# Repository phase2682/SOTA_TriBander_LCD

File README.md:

# SOTA_TriBander_LCD
Replacing the LED display with a LCD on the SOTA  Tri-Bander CW transceiver
https://www.ai6xg.com/post/lcd-display-for-the-kd1jv-tribander

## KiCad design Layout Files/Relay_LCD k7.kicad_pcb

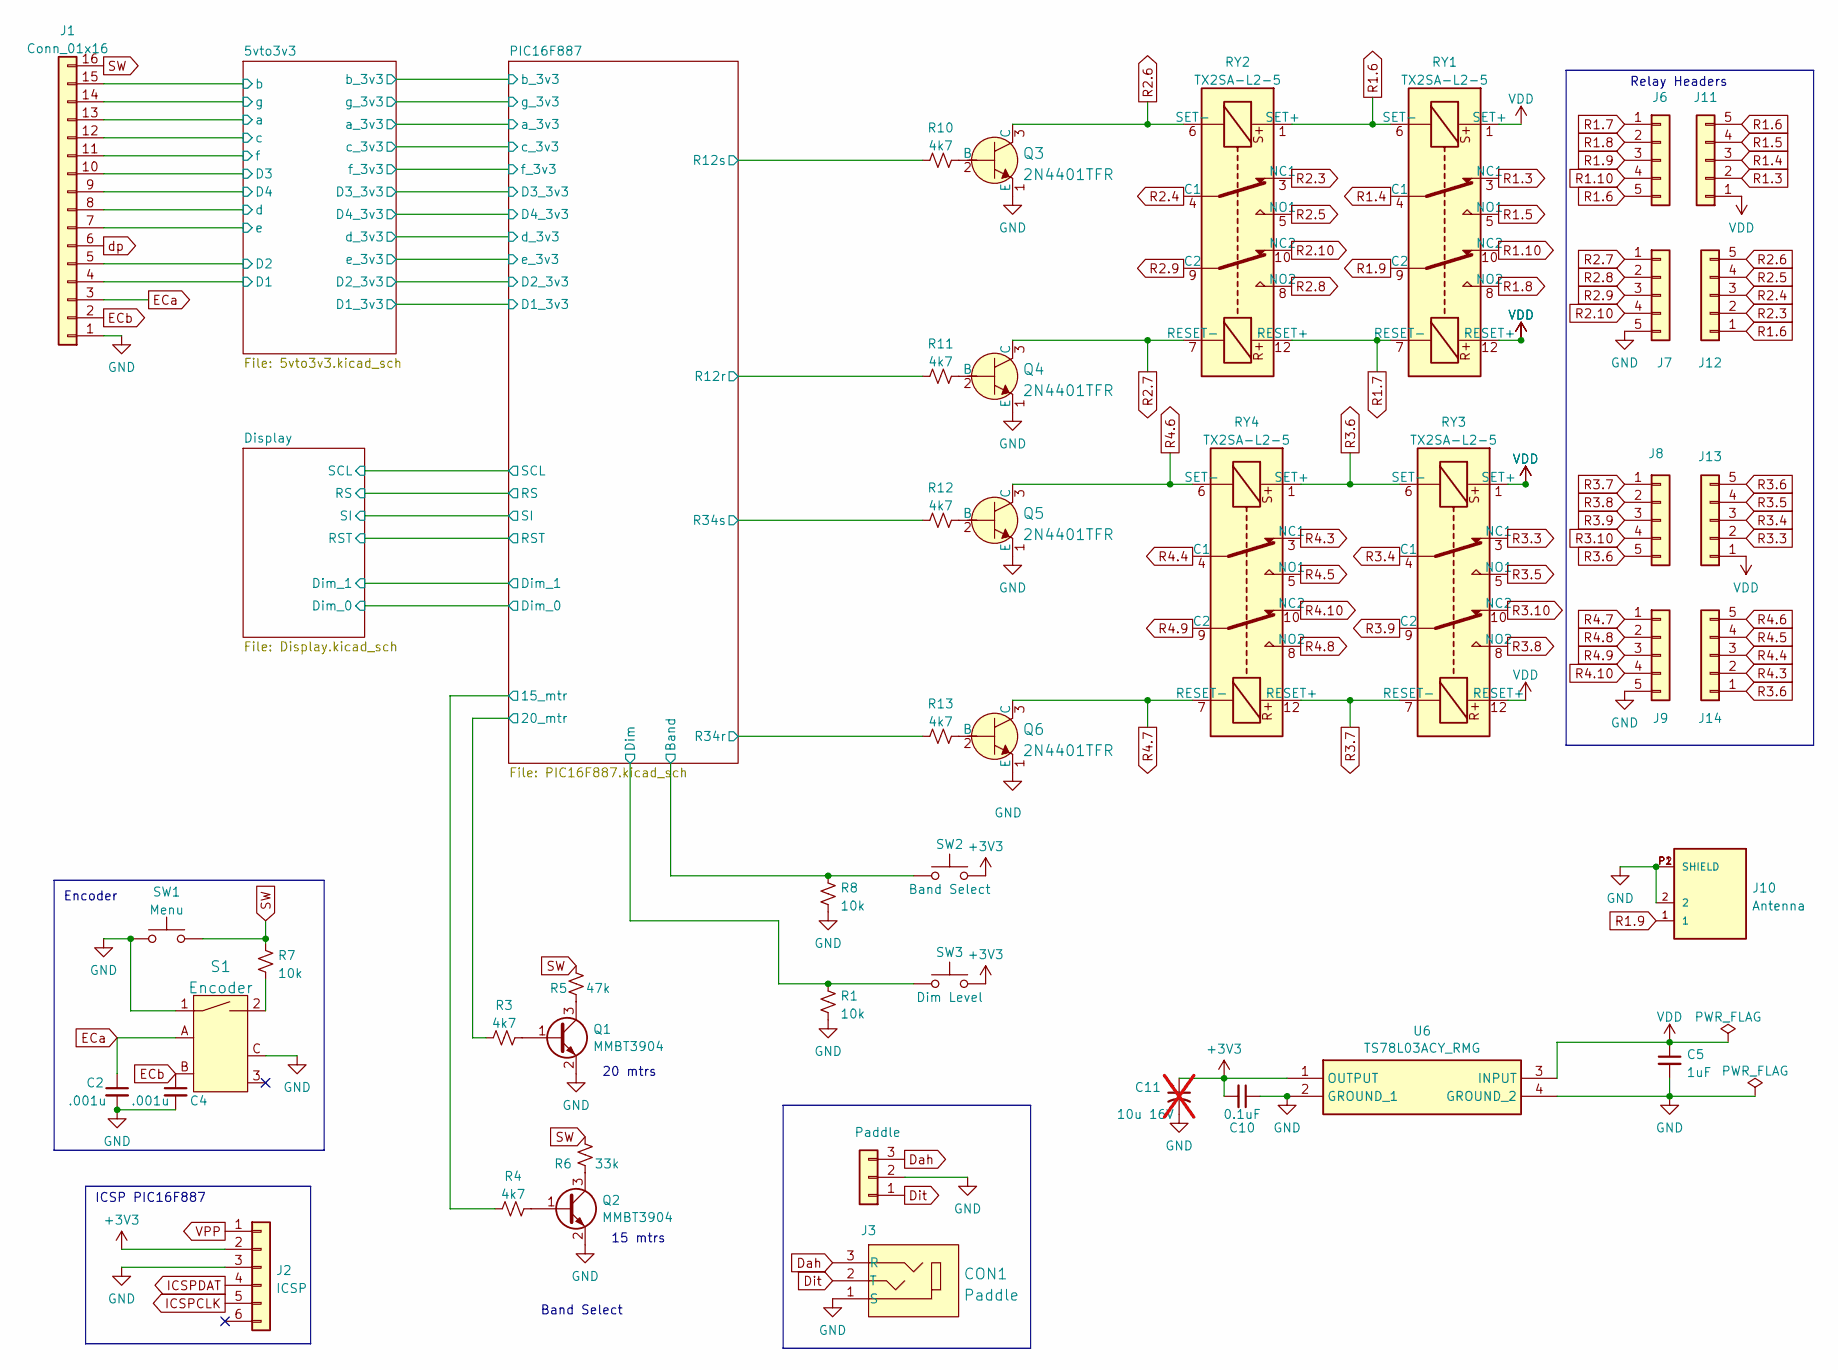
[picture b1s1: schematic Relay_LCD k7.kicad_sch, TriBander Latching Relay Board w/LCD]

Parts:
C2, C4: .001u; C_Disc_D3.4mm_W2.1mm_P2.50mm
C5: 1uF; C_1206_3216Metric_Pad1.33x1.80mm_HandSolder
C10: 0.1uF; C_1206_3216Metric_Pad1.33x1.80mm_HandSolder
C11: 10u 16V; CP_Radial_D6.3mm_P2.50mm; not fitted
CON1: Paddle; CUI_SJ1-3513N round pin; MPN SJ1-3523N; Digi-Key_PN CP1-3523N-ND
J1: Conn_01x16; PinHeader_1x16_P2.54mm_Vertical
J2: ICSP; PinHeader_1x06_P2.54mm_Vertical
J3: Paddle; PinHeader_1x03_P2.54mm_Vertical
J6, J7, J8, J9, J11, J12, J13, J14: Conn_01x05; PinHeader_1x05_P2.54mm_Vertical
J10: Antenna; CONN_1-1337543-0
Q1, Q2: MMBT3904; SOT-23
Q3, Q4, Q5, Q6: 2N4401TFR; TO-92-3_Formed_Leads; MPN 2N4401TFR; Digi-Key_PN 2N4401D26ZCT-ND
R1, R7, R8: 10k; R_1206_3216Metric_Pad1.30x1.75mm_HandSolder
R3, R4: 4k7; R_1206_3216Metric_Pad1.30x1.75mm_HandSolder
R5: 47k; R_1206_3216Metric_Pad1.30x1.75mm_HandSolder
R6: 33k; R_1206_3216Metric_Pad1.30x1.75mm_HandSolder
R10, R11, R12, R13: 4k7; R THT .25W minP
RY1, RY2, RY3, RY4: TX2SA-L2-5; Relay_DPDT_Kemet_EE2_NU_DoubleCoil
S1: Encoder; Rotary_Encoder_Switched_PEC11R; MPN PEC11R-4215F-S0024; Digi-Key_PN PEC11R-4215F-S0024-ND
SW1: Menu; SW_PUSH_6mm
SW2: Band Select; SW_PUSH_6mm
SW3: Dim Level; SW_PUSH_6mm
U6: TS78L03ACY_RMG; SOT-89-3_Handsoldering; Mouser Part Number 821-TS78L03ACYRMG

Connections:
+3V3: C10.2, C11.1, J2.2, SW2.2, SW3.2, U6.1 (OUTPUT); also elsewhere on the board
/5vto3v3/D1: J1.4; also elsewhere on the board
/5vto3v3/D2: J1.5; also elsewhere on the board
/5vto3v3/D3: J1.10; also elsewhere on the board
/5vto3v3/D4: J1.9; also elsewhere on the board
/5vto3v3/a: J1.13; also elsewhere on the board
/5vto3v3/b: J1.15; also elsewhere on the board
/5vto3v3/c: J1.12; also elsewhere on the board
/5vto3v3/d: J1.8; also elsewhere on the board
/5vto3v3/e: J1.7; also elsewhere on the board
/5vto3v3/f: J1.11; also elsewhere on the board
/5vto3v3/g: J1.14; also elsewhere on the board
/PIC16F887/15_mtr: R4.1; also elsewhere on the board
/PIC16F887/20_mtr: R3.1; also elsewhere on the board
/PIC16F887/Band: R8.2, SW2.1; also elsewhere on the board
/PIC16F887/Dim: R1.2, SW3.1; also elsewhere on the board
/PIC16F887/R12r: R11.1; also elsewhere on the board
/PIC16F887/R12s: R10.1; also elsewhere on the board
/PIC16F887/R34r: R13.1; also elsewhere on the board
/PIC16F887/R34s: R12.1; also elsewhere on the board
Dah: CON1.3 (R), J3.3
Dit: CON1.2 (T), J3.1
ECa: C2.1, J1.3, S1.A (CH_A)
ECb: C4.1, J1.2, S1.B (CH_B)
GND: C2.2, C4.2, C5.2, C10.1, C11.2, CON1.1 (S), J1.1, J2.3, J3.2, J7.5, J9.5, J10.2, J10.P1 (SHIELD), J10.P2 (SHIELD), Q1.2 (E), Q2.2 (E), Q3.1 (E), Q4.1 (E), Q5.1 (E), Q6.1 (E), R1.1, R8.1, S1.1, S1.C (COM), SW1.1, U6.2 (GROUND_1), U6.4 (GROUND_2); also elsewhere on the board
ICSPCLK: J2.5; also elsewhere on the board
ICSPDAT: J2.4; also elsewhere on the board
unnamed: Q1.1 (B), R3.2
unnamed: Q1.3 (C), R5.2
unnamed: Q2.1 (B), R4.2
unnamed: Q2.3 (C), R6.2
unnamed: Q3.2 (B), R10.2
unnamed: Q4.2 (B), R11.2
unnamed: Q5.2 (B), R12.2
unnamed: Q6.2 (B), R13.2
unnamed: R7.2, S1.2
R1.3: J11.2, RY1.3 (NC1)
R1.4: J11.3, RY1.4 (C1)
R1.5: J11.4, RY1.5 (NO1)
R1.6: J6.5, J11.5, J12.1, RY1.6 (SET-), RY2.1 (SET+)
R1.7: J6.1, RY1.7 (RESET-), RY2.12 (RESET+)
R1.8: J6.2, RY1.8 (NO2)
R1.9: J6.3, J10.1, RY1.9 (C2)
R1.10: J6.4, RY1.10 (NC2)
R2.3: J12.2, RY2.3 (NC1)
R2.4: J12.3, RY2.4 (C1)
R2.5: J12.4, RY2.5 (NO1)
R2.6: J12.5, Q3.3 (C), RY2.6 (SET-)
R2.7: J7.1, Q4.3 (C), RY2.7 (RESET-)
R2.8: J7.2, RY2.8 (NO2)
R2.9: J7.3, RY2.9 (C2)
R2.10: J7.4, RY2.10 (NC2)
R3.3: J13.2, RY3.3 (NC1)
R3.4: J13.3, RY3.4 (C1)
R3.5: J13.4, RY3.5 (NO1)
R3.6: J8.5, J13.5, J14.1, RY3.6 (SET-), RY4.1 (SET+)
R3.7: J8.1, RY3.7 (RESET-), RY4.12 (RESET+)
R3.8: J8.2, RY3.8 (NO2)
R3.9: J8.3, RY3.9 (C2)
R3.10: J8.4, RY3.10 (NC2)
R4.3: J14.2, RY4.3 (NC1)
R4.4: J14.3, RY4.4 (C1)
R4.5: J14.4, RY4.5 (NO1)
R4.6: J14.5, Q5.3 (C), RY4.6 (SET-)
R4.7: J9.1, Q6.3 (C), RY4.7 (RESET-)
R4.8: J9.2, RY4.8 (NO2)
R4.9: J9.3, RY4.9 (C2)
R4.10: J9.4, RY4.10 (NC2)
SW: J1.16, R5.1, R6.1, R7.1, SW1.2
VDD: C5.1, J11.1, J13.1, RY1.1 (SET+), RY1.12 (RESET+), RY3.1 (SET+), RY3.12 (RESET+), U6.3 (INPUT)
VPP: J2.1; also elsewhere on the board
dp: J1.6

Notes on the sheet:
20 mtrs
15 mtrs
Relay Headers
ICSP PIC16F887
Encoder
Band Select

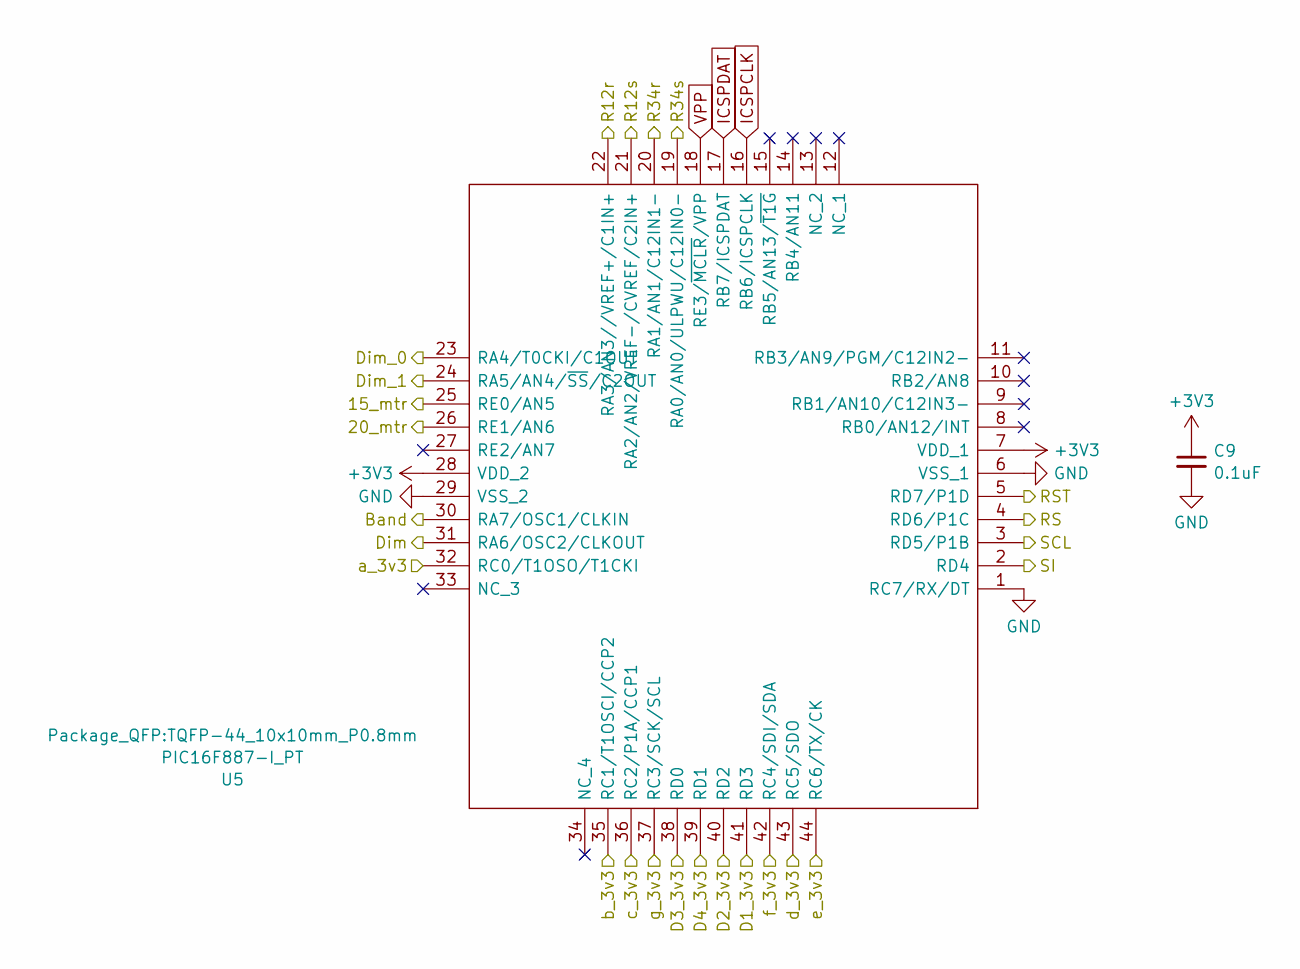
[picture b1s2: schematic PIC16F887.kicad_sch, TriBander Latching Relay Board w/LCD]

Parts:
C9: 0.1uF; C_1206_3216Metric_Pad1.33x1.80mm_HandSolder
U5: PIC16F887-I_PT; TQFP-44_10x10mm_P0.8mm; Mouser Part Number 579-PIC16F887-I/PT

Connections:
+3V3: C9.1, U5.7 (VDD_1), U5.28 (VDD_2); also elsewhere on the board
/5vto3v3/D1_3v3: U5.41 (RD3); also elsewhere on the board
/5vto3v3/D2_3v3: U5.40 (RD2); also elsewhere on the board
/5vto3v3/D3_3v3: U5.38 (RD0); also elsewhere on the board
/5vto3v3/D4_3v3: U5.39 (RD1); also elsewhere on the board
/5vto3v3/a_3v3: U5.32 (RC0/T1OSO/T1CKI); also elsewhere on the board
/5vto3v3/b_3v3: U5.35 (RC1/T1OSCI/CCP2); also elsewhere on the board
/5vto3v3/c_3v3: U5.36 (RC2/P1A/CCP1); also elsewhere on the board
/5vto3v3/d_3v3: U5.43 (RC5/SDO); also elsewhere on the board
/5vto3v3/e_3v3: U5.44 (RC6/TX/CK); also elsewhere on the board
/5vto3v3/f_3v3: U5.42 (RC4/SDI/SDA); also elsewhere on the board
/5vto3v3/g_3v3: U5.37 (RC3/SCK/SCL); also elsewhere on the board
/Display/Dim_0: U5.23 (RA4/T0CKI/C1OUT); also elsewhere on the board
/Display/Dim_1: U5.24 (RA5/AN4/~SS/C2OUT); also elsewhere on the board
/Display/RS: U5.4 (RD6/P1C); also elsewhere on the board
/Display/RST: U5.5 (RD7/P1D); also elsewhere on the board
/Display/SCL: U5.3 (RD5/P1B); also elsewhere on the board
/Display/SI: U5.2 (RD4); also elsewhere on the board
/PIC16F887/15_mtr: U5.25 (RE0/AN5); also elsewhere on the board
/PIC16F887/20_mtr: U5.26 (RE1/AN6); also elsewhere on the board
/PIC16F887/Band: U5.30 (RA7/OSC1/CLKIN); also elsewhere on the board
/PIC16F887/Dim: U5.31 (RA6/OSC2/CLKOUT); also elsewhere on the board
/PIC16F887/R12r: U5.22 (RA3/AN3//VREF+/C1IN+); also elsewhere on the board
/PIC16F887/R12s: U5.21 (RA2/AN2/VREF-/CVREF/C2IN+); also elsewhere on the board
/PIC16F887/R34r: U5.20 (RA1/AN1/C12IN1-); also elsewhere on the board
/PIC16F887/R34s: U5.19 (RA0/AN0/ULPWU/C12IN0-); also elsewhere on the board
GND: C9.2, U5.1 (RC7/RX/DT), U5.6 (VSS_1), U5.29 (VSS_2); also elsewhere on the board
ICSPCLK: U5.16 (RB6/ICSPCLK); also elsewhere on the board
ICSPDAT: U5.17 (RB7/ICSPDAT); also elsewhere on the board
VPP: U5.18 (RE3/~MCLR/VPP); also elsewhere on the board

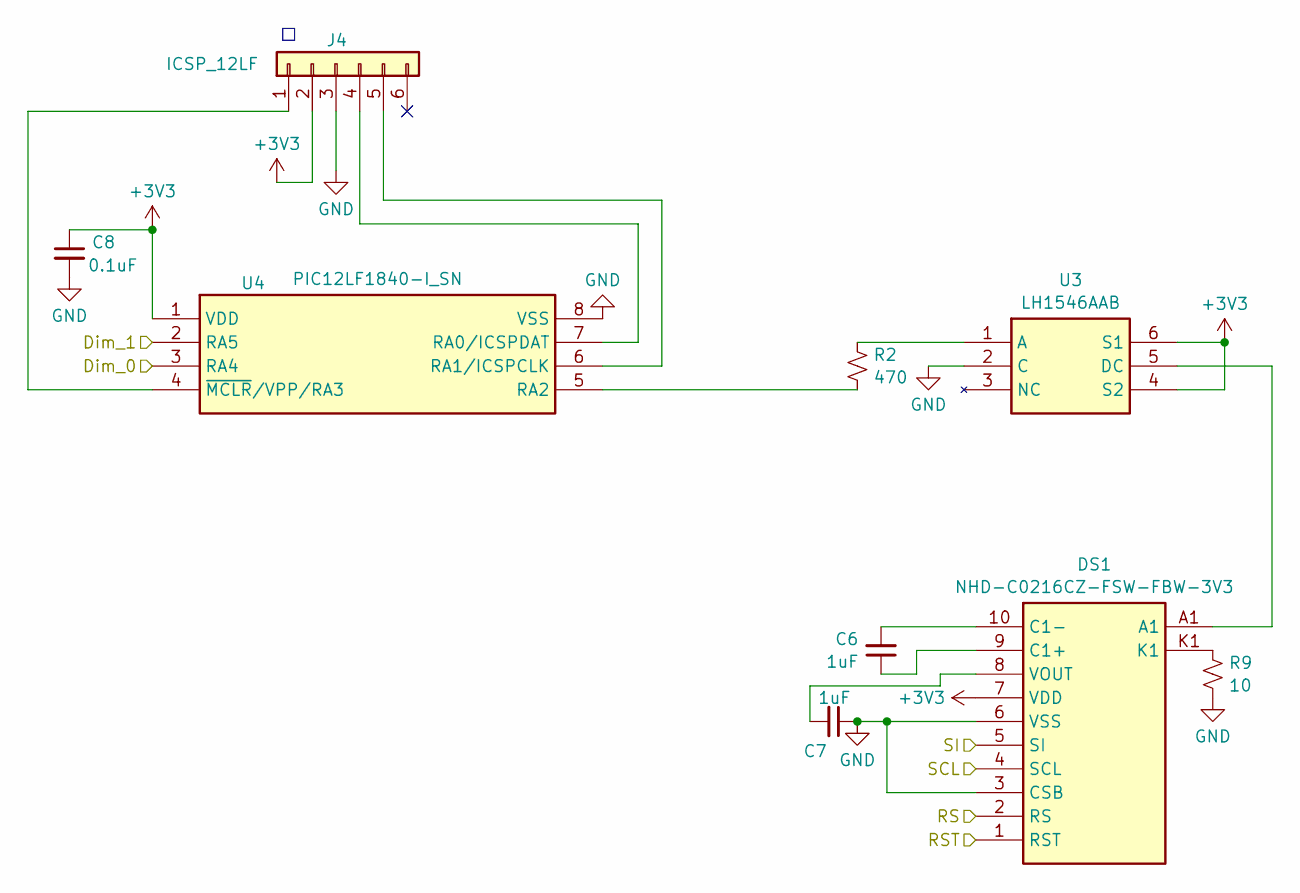
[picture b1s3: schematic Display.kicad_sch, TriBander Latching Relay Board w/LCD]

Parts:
C6, C7: 1uF; C_1206_3216Metric_Pad1.33x1.80mm_HandSolder
C8: 0.1uF; C_1206_3216Metric_Pad1.33x1.80mm_HandSolder
DS1: NHD-C0216CZ-FSW-FBW-3V3; NHDC0216CZFSWFBW3V3; Mouser Part Number 763-C0216CZ-FSWFBW3V
J4: ICSP_12LF; PinHeader_1x06_P2.54mm_Vertical
R2: 470; R_1206_3216Metric_Pad1.30x1.75mm_HandSolder
R9: 10; R_1206_3216Metric_Pad1.30x1.75mm_HandSolder
U3: LH1546AAB; SOP254P980X425-6N; Mouser Part Number 782-LH1546AABTR
U4: PIC12LF1840-I_SN; SO-8_3.9x4.9mm_P1.27mm; Mouser Part Number 579-PIC12LF1840-I/SN

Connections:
+3V3: C8.1, DS1.7 (VDD), J4.2, U3.4 (S2), U3.6 (S1), U4.1 (VDD); also elsewhere on the board
/Display/Dim_0: U4.3 (RA4); also elsewhere on the board
/Display/Dim_1: U4.2 (RA5); also elsewhere on the board
/Display/RS: DS1.2 (RS); also elsewhere on the board
/Display/RST: DS1.1 (RST); also elsewhere on the board
/Display/SCL: DS1.4 (SCL); also elsewhere on the board
/Display/SI: DS1.5 (SI); also elsewhere on the board
GND: C7.1, C8.2, DS1.3 (CSB), DS1.6 (VSS), J4.3, R9.2, U3.2 (C), U4.8 (VSS); also elsewhere on the board
unnamed: C6.1, DS1.9 (C1+)
unnamed: C6.2, DS1.10 (C1-)
unnamed: DS1.K1, R9.1
unnamed: C7.2, DS1.8 (VOUT)
unnamed: J4.1, U4.4 (~MCLR/VPP/RA3)
unnamed: J4.4, U4.7 (RA0/ICSPDAT)
unnamed: J4.5, U4.6 (RA1/ICSPCLK)
unnamed: R2.1, U3.1 (A)
unnamed: DS1.A1, U3.5 (DC)
unnamed: R2.2, U4.5 (RA2)

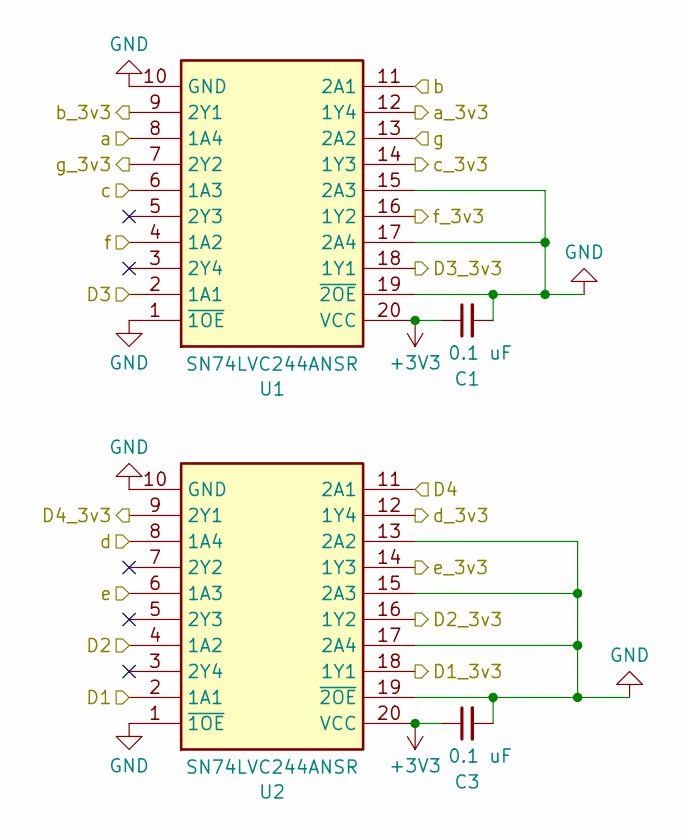
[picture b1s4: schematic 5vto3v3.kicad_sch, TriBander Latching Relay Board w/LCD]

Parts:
C1, C3: 0.1 uF; C_1206_3216Metric_Pad1.33x1.80mm_HandSolder
U1, U2: SN74LVC244ANSR; SO-20_5.3x12.6mm_P1.27mm; Mouser Part Number 595-SN74LVC244ANSR

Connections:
+3V3: C1.1, C3.1, U1.20 (VCC), U2.20 (VCC); also elsewhere on the board
/5vto3v3/D1: U2.2 (1A1); also elsewhere on the board
/5vto3v3/D1_3v3: U2.18 (1Y1); also elsewhere on the board
/5vto3v3/D2: U2.4 (1A2); also elsewhere on the board
/5vto3v3/D2_3v3: U2.16 (1Y2); also elsewhere on the board
/5vto3v3/D3: U1.2 (1A1); also elsewhere on the board
/5vto3v3/D3_3v3: U1.18 (1Y1); also elsewhere on the board
/5vto3v3/D4: U2.11 (2A1); also elsewhere on the board
/5vto3v3/D4_3v3: U2.9 (2Y1); also elsewhere on the board
/5vto3v3/a: U1.8 (1A4); also elsewhere on the board
/5vto3v3/a_3v3: U1.12 (1Y4); also elsewhere on the board
/5vto3v3/b: U1.11 (2A1); also elsewhere on the board
/5vto3v3/b_3v3: U1.9 (2Y1); also elsewhere on the board
/5vto3v3/c: U1.6 (1A3); also elsewhere on the board
/5vto3v3/c_3v3: U1.14 (1Y3); also elsewhere on the board
/5vto3v3/d: U2.8 (1A4); also elsewhere on the board
/5vto3v3/d_3v3: U2.12 (1Y4); also elsewhere on the board
/5vto3v3/e: U2.6 (1A3); also elsewhere on the board
/5vto3v3/e_3v3: U2.14 (1Y3); also elsewhere on the board
/5vto3v3/f: U1.4 (1A2); also elsewhere on the board
/5vto3v3/f_3v3: U1.16 (1Y2); also elsewhere on the board
/5vto3v3/g: U1.13 (2A2); also elsewhere on the board
/5vto3v3/g_3v3: U1.7 (2Y2); also elsewhere on the board
GND: C1.2, C3.2, U1.1 (~1OE), U1.10 (GND), U1.15 (2A3), U1.17 (2A4), U1.19 (~2OE), U2.1 (~1OE), U2.10 (GND), U2.13 (2A2), U2.15 (2A3), U2.17 (2A4), U2.19 (~2OE); also elsewhere on the board

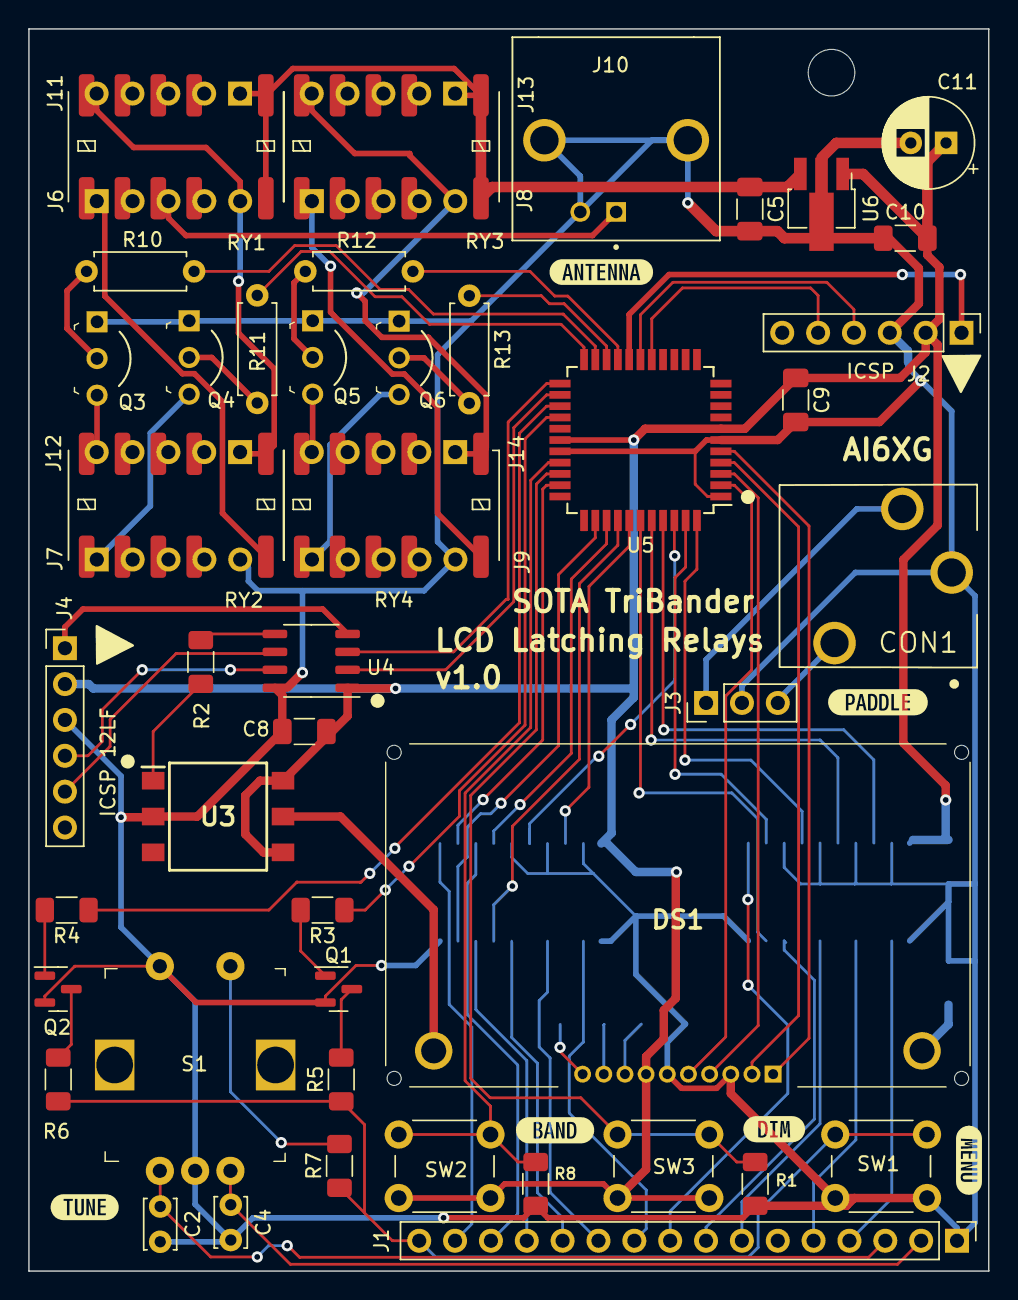
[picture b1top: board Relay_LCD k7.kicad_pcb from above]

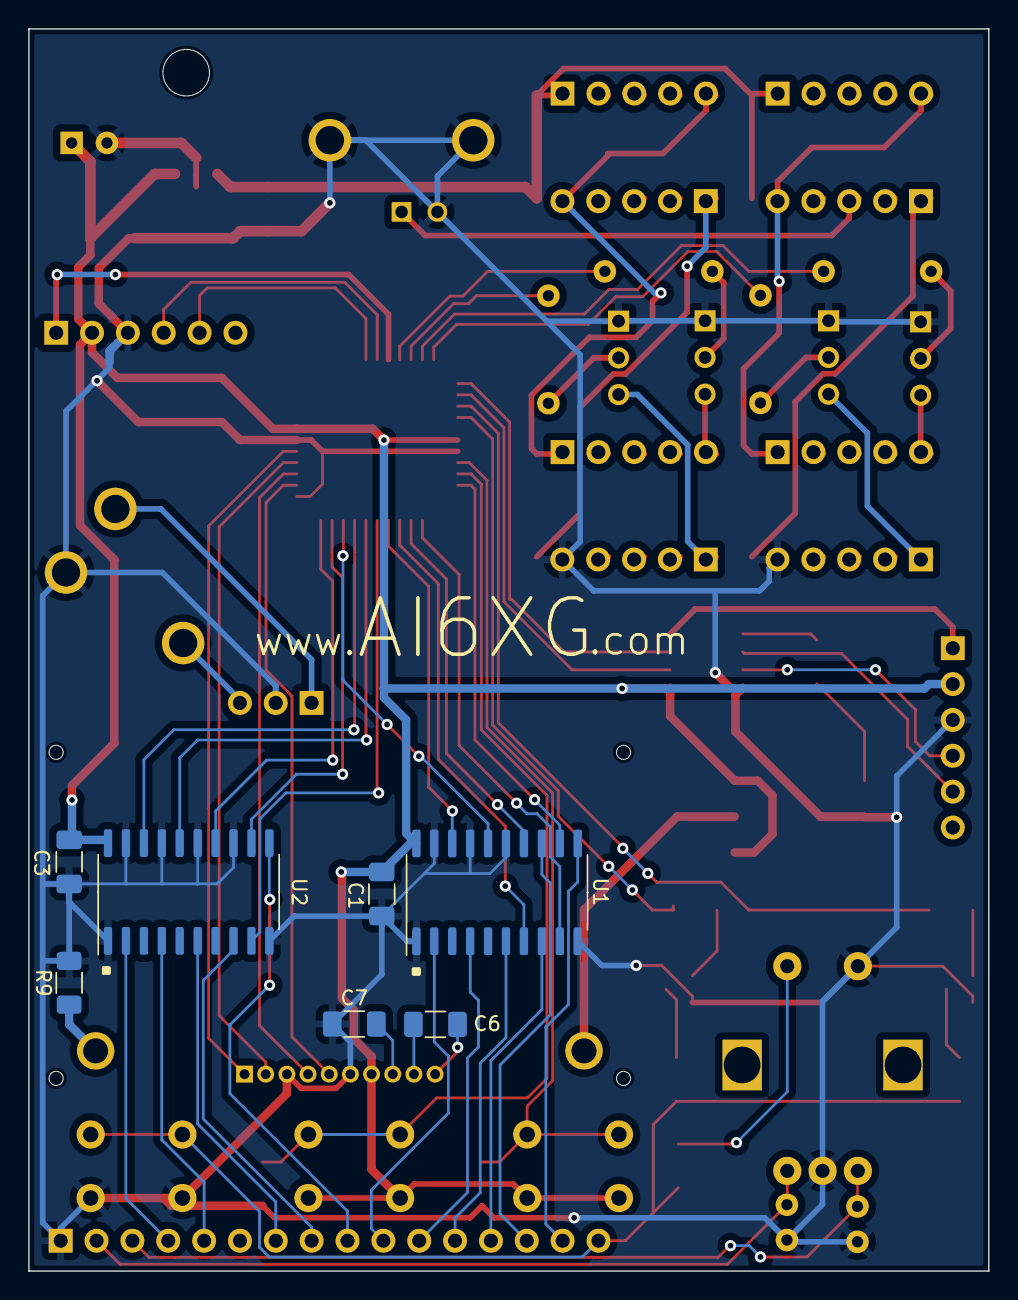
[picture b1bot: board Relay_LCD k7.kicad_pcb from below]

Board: 2 copper layers, 68.0 x 88.0 mm, 65 parts (7 on the bottom side), 98 nets.

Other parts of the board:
kibuzzard-659F9941: G***; kibuzzard-659F9941
kibuzzard-659F9955: G***; kibuzzard-659F9955
kibuzzard-6406D9A6: G***; kibuzzard-6406D9A6
kibuzzard-6406D9EC: G***; kibuzzard-6406D9EC
kibuzzard-6406DC87: G***; kibuzzard-6406DC87
kibuzzard-6407CA45: G***; kibuzzard-6407CA45

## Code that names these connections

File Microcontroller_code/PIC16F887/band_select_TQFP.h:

/* 
 * File:   band select TQFP.h
 * Author: Dan Koellen AI6XG
 *
 * Created on November 10, 2023, 5:25 PM
 * revised for TQFP on January 24, 2024
 */

#include <xc.h> // include processor files - each processor file is guarded.

//Definitions for band set
#define band_set	RA7                 //set input to advance band 
#define _15_mtr     RE0                 //15 meters band set output
#define _20_mtr     RE1                 //20 meters band set output

#define R12s        RA2                 //relays 1 and 2 set output
#define R12r        RA3                 //relays 1 and 2 reset output
#define R34s        RA0                 //relays 3 and 4 set output
#define R34r        RA1                 //relays 3 and 4 reset output
#define relay_pulse_dur 6               //relay pulse duration timer0_events output

unsigned char 	band = 0;            	//0->40 mtrs, 1->20 mtrs, 2->15 mtrs
unsigned char 	previous_band = 3;		//forces band <> previous_band at startup
unsigned int 	state_band = 0;			//debounce state holder

unsigned int   R12s_time = 0;          //time that R12 is set
unsigned int   R12r_time = 0;          //time that R12 is reset
unsigned int   R34s_time = 0;          //time that R34 is set
unsigned int   R34r_time = 0;          //time that R34 is reset

//declare functions

//returns 0 after duration # of timer0_events, otherwise 1
unsigned char 	DurationClear(unsigned int start, unsigned char duration,
        unsigned int reset, unsigned int events);

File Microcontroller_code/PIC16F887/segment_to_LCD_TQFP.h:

/* 
 * File:   segment_to_LCD_TQFP.h
 * Author: Dan Koellen AI6XG
 *
 * Created on November 9, 2023, 3:42 PM
 *  revised for TQFP on January 24, 2024
 */

#include <xc.h> // include processor files - each processor file is guarded.

//definitions for segment and digits

#define D1          RD3         //Digit 1 input
#define D2          RD2         //Digit 2 input
#define D3          RD0         //Digit 3 input
#define D4          RD1         //Digit 4 input

#define seg_b       RC1         //segment b input
#define seg_e       RC6         //segment e input
#define seg_dp      RC7         //decimal point input
#define seg_d       RC5         //segment d input
#define seg_g       RC3         //segment g input
#define seg_a       RC0         //segment a input
#define seg_c       RC2         //segment c input
#define seg_f       RC4         //segment f input

/*
 Each definition is for segments of the seven segment LED that would be active
 * for each symbol.  The numerical value is the port value for the segments that
 * are active.  
 * Also determined by active low (common anode) or active high(common cathode).
 * For example for the following port definitions 
#define seg_b       RC1         //segment b input
#define seg_e       RC6         //segment e input
#define seg_dp      RC7         //decimal point input
#define seg_d       RC5         //segment d input
#define seg_g       RC3         //segment g input
#define seg_a       RC0         //segment a input
#define seg_c       RC2         //segment c input
#define seg_f       RC4         //segment f input
 * 
 * The character two on a seven segment would be segments a,b,d,e and g active
 * the PORTC value for the character two would be 0b01101011 or 0x6B active high 
 * and 0b10010100 or 0x94 active low
 */

//rev 1.0 PCB has fixed RC7 (dp) grounded (active) rather than high (inactive)
//rest of segments are active low, inactive high
#define zero    0x08            //0
#define one     0x79            //1
#define two     0x14            //2
#define three   0x50            //3
#define four    0x61            //4
#define five    0x42            //5
#define six     0x03            //6
#define seven   0x78            //7
#define eight   0x00            //8
#define nine    0x60            //9
#define blank   0x7F            //no segments active
#define r       0x37            //r
#define dash    0x77            //-
#define C       0x0E            //C
#define o       0x13            //o
#define t       0x07            //t
#define equal   0x76            //=



unsigned char   d_4 = 0;           //digit 4 data rightmost digit
unsigned char   d_4_old = 1;        //old digit 4 data

unsigned char   d_3 = 0;           //digit 3 data
unsigned char   d_3_old = 1;        //old digit 3 data

unsigned char   d_2 = 0;           //digit 2 data
unsigned char   d_2_old = 1;        //old digit 2 data

unsigned char   d_1 = 0;           //digit 1 data leftmost digit
unsigned char   d_1_old = 1;        //old digit 1 data

unsigned char   digit_changed = 0;  //flag for digit change


 
//declare functions

//updates display with character representative of c
extern void seg_write_lcd(unsigned char c);

//updates display with character representative of c_# (digits 1 -4)
extern void update_display(unsigned char pos_1, unsigned char pos_2,unsigned char pos_3,
        unsigned char pos_4, unsigned char c_1, unsigned char c_2, unsigned char c_3,
        unsigned char c_4);

//returns the value number representative of c
extern unsigned char seg_to_value(unsigned char c);

//updates display with character representative of c_# (digits 1 -4)
//input of value of digit of c_# (digits 1 -4), 0 - 9  inclusive
extern void update_display_value(unsigned char pos_1, unsigned char pos_2,unsigned char pos_3,
        unsigned char pos_4, unsigned char c_1, unsigned char c_2, unsigned char c_3,
        unsigned char c_4);

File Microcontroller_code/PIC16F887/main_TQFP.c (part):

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int offset_40 = -1;             //offset for 40 meters
int offset_20 = -1;             //offset for 20 meters
int offset_15 = -2;             //offset for 15 meters
int offset  = 0;                //offset for selected band



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

//dim level definitions
#define dim_set     RA6                 //input pin for setting LCD backlight level
#define dim_0       RA4                 //output dim level bit 0
#define dim_1       RA5                 //outpur dim level bit 1


unsigned char 	dim = 0;            	//dim level
unsigned char   previous_dim = 0;       //previous dim level
unsigned int 	state_dim = 0;			//debounce dim state holder



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


if(band_set) two_line = 1;      //set two line flag if band set is pressed
                                //at power on

RST = 1;                    //RST must high before going into initialization
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__delay_ms(50);

//reset relays to band = 0 --> 40 meters
 R12r = 1;                   //reset relays 1 and 2
 R34r = 1;                   //reset relays 3 and 4
 __delay_ms(3);              //3 mSec pulse
  R12r = 0;                   //reset relays 1 and 2
  R34r = 0;                   //reset relays 3 and 4
 

//Initial two line Screen for 3 seconds
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		if (state_band == 0xF000)           //true if band_set set
			{
			band++;							//increment band to next band
			if (band > 2) band = 0;         //go back to initial band
            
            }
        
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		if (state_dim == 0xF000)           //true if dim_set set
			{
			dim++;							//increment dim to next dim level
			if (dim > 5) dim = 0;         //go back initial dim level
            
            }

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    {
        if (band == 0) 					//40 meters
        {
            _15_mtr = 0;                //band set to 15 meter set resistor
            _20_mtr = 0;                //band set to 20 meter set resistor

            R12r = 1;                   //reset relays 1 and 2
            R34r = 1;                   //reset relays 3 and 4
            R12r_time = R34r_time = timer0_events;
                                        //time relay pulse starts

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        if (band == 1)					//20 meters	
            {

            _15_mtr = 0;                //band set to 15 meter set resistor
            _20_mtr = 1;                //band set to 20 meter set resistor

            R12r = 1;                   //reset relays 1 and 2
            R34s = 1;                   //set relays 3 and 4
            R12r_time = R34s_time = timer0_events;
                                        //time relay pulse starts

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        if (band  == 2)					//15 meters
            {

            _15_mtr = 1;                //band set to 15 meter set resistor
            _20_mtr = 0;                //band set to 20 meter set resistor

            R12s = 1;                   //set relays 1 and 2
     
            R12s_time = timer0_events;   //time relay pulse starts

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        {
         if (dim == 0)                  //LCD backlight off
         {
             dim_0 = 0;
             dim_1 = 0;
         }               //end 0% if
         
         if (dim == 1 || dim == 5)       //LCD backlight 25%
         {
             dim_0 = 1;
             dim_1 = 0;
         }                //end 25% if
         
         if (dim == 2 || dim == 4)       //LCD backlight 50%
         {
             dim_0 = 0;
             dim_1 = 1;
         }               //end 50% if
         
         if (dim == 3)                  //LCD backlight 100%
         {
             dim_0 = 1;
             dim_1 = 1;
         }               //end 100% if
         previous_dim = dim;
        }               //end previous_dim if
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
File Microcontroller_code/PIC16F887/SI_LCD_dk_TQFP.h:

/* 
 * File:   SI_LCD_dk_TQFP.h
 * Author: Dan Koellen 
 * Comments:
 * Revision history: 
 * * revised for TQFP on January 24, 2024
 */


#include <xc.h> // include processor files - each processor file is guarded.  


// define IOs for logic signals
#define SI          RD4         //Serial Data To LCD
#define SCL         RD5         //Serial Clock
#define RS          RD6         //Register Select 0=command 1=data
#define RST         RD7         //Active Low Reset

unsigned char two_line = 0;     //two line font flag

//CSB not used for only one display, tie to ground
//#define CSB         RD3         //Active Low Chip Select



//function declaration

/* write a character to the LCD */
extern void lcd_data (unsigned char d);

/* write a command to the LCD */
extern void lcd_command(unsigned char c);

/* intialize the LCD - call before anything else */
extern void lcd_initialize (void);

/* write a string of characters to the LCD */
extern void lcd_puts(const char * s);

/* Go to the specified position on line 1*/
extern void lcd_goto_one(unsigned char p);

/* Go to the specified position on line 2*/
extern void lcd_goto_two(unsigned char pos);

/* Clear and home the LCD */
extern void lcd_clear(void);

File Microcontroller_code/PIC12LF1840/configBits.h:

/* 
 * File:   configBits.h
 * Author: Dan Koellen AI6XG
 *
 * Created on December 21, 2023, 11:05 PM
 */

#ifndef CONFIGBITS_H
#define	CONFIGBITS_H

#ifdef	__cplusplus
extern "C" {
#endif

// PIC12LF1840 Configuration Bit Settings
// 'C' source line config statements
// CONFIG1
#pragma config FOSC = INTOSC    // Oscillator Selection (INTOSC oscillator: I/O function on CLKIN pin)
#pragma config WDTE = OFF       // Watchdog Timer Enable (WDT disabled)
#pragma config PWRTE = OFF      // Power-up Timer Enable (PWRT disabled)
#pragma config MCLRE = OFF      // MCLR Pin Function Select (MCLR/VPP pin function is digital input)
#pragma config CP = OFF         // Flash Program Memory Code Protection (Program memory code protection is disabled)
#pragma config CPD = OFF        // Data Memory Code Protection (Data memory code protection is disabled)
#pragma config BOREN = OFF      // Brown-out Reset Enable (Brown-out Reset disabled)
#pragma config CLKOUTEN = OFF   // Clock Out Enable (CLKOUT function is disabled. I/O or oscillator function on the CLKOUT pin)
#pragma config IESO = OFF       // Internal/External Switchover (Internal/External Switchover mode is disabled)
#pragma config FCMEN = OFF      // Fail-Safe Clock Monitor Enable (Fail-Safe Clock Monitor is disabled)

// CONFIG2
#pragma config WRT = OFF        // Flash Memory Self-Write Protection (Write protection off)
#pragma config PLLEN = OFF      // PLL Enable (4x PLL disabled)
#pragma config STVREN = OFF     // Stack Overflow/Underflow Reset Enable (Stack Overflow or Underflow will not cause a Reset)
#pragma config BORV = LO        // Brown-out Reset Voltage Selection (Brown-out Reset Voltage (Vbor), low trip point selected.)
#pragma config DEBUG = OFF      // In-Circuit Debugger Mode (In-Circuit Debugger disabled, ICSPCLK and ICSPDAT are general purpose I/O pins)
#pragma config LVP = OFF        // Low-Voltage Programming Enable (High-voltage on MCLR/VPP must be used for programming)

// #pragma config statements should precede project file includes.
// Use project enums instead of #define for ON and OFF.

//#include <xc.h>




#ifdef	__cplusplus
}
#endif

#endif	/* CONFIGBITS_H */

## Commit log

2024-05-09 Create Layout Files
2024-05-09 Create test
2024-05-09 Create =
2024-05-09 Create 5
